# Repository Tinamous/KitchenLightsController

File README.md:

# KitchenLightsController
IoT Particle Photon powered kitchen lights controller. Switch and dim LED and halogen lights.

Assembly
--------

Mount SMD components.

Solder on JP1, 12V DC power in.
For 2 & 3 min molex headers use sponge to keep connectors in place. Solder single pin, and then reflow that pushing the connector square to the board.
Solder JP35, JP47, JP34, JP48, JP49 - 3 pin molex connectors. Farnell: 9731156
Solder JP201, 202, 203, 301, 302, 303, 401, 402, 403. Optionally solder JP501 or 502. (or both). Fit only as many as you need. Farnell: 9731148

Solder JP43 (terminal block).

Fit C1 (330nF. Farnell: 1902922
Solder headers for Photon. eBay.
F1 Fuse folder. Farnell: 1453528
IC1 7805 or eBay switching version
C4 1000uF 16v. Farnell: 9693610
Connect JP37 if using onboard 5V supply for NeoPixels.
Fit X2 if using USB 5V switch.
Fuse 5A quick blow: Farnell: 1354578

Before powering up:
Check 12V rails for short circuit.
Check 5V rails for short.
Check 3v3 rails for short.

Power up using low current limit on bench PSU (ca. 50m-100A)
Check 5v rail and adjust reg as needed. Expect 3 LEDs to light (12v, 5V and ext. 5V). 14-20mA consumption.

V2.03 Changed:
Moved via under Photon to not mess with silk screen.
Moved OSH logo to near USB A Socket to give it more room and allow the 5V LED to be reverse mounted.
TODO:
Move 5V LED to be reverse mounted
Change 5V usb switched connector to be 0.1" molex not screw terminal.
Correct Channel 4 & Ext. 5V supply screw terminals to be the correct way around (double line on outside of the board).

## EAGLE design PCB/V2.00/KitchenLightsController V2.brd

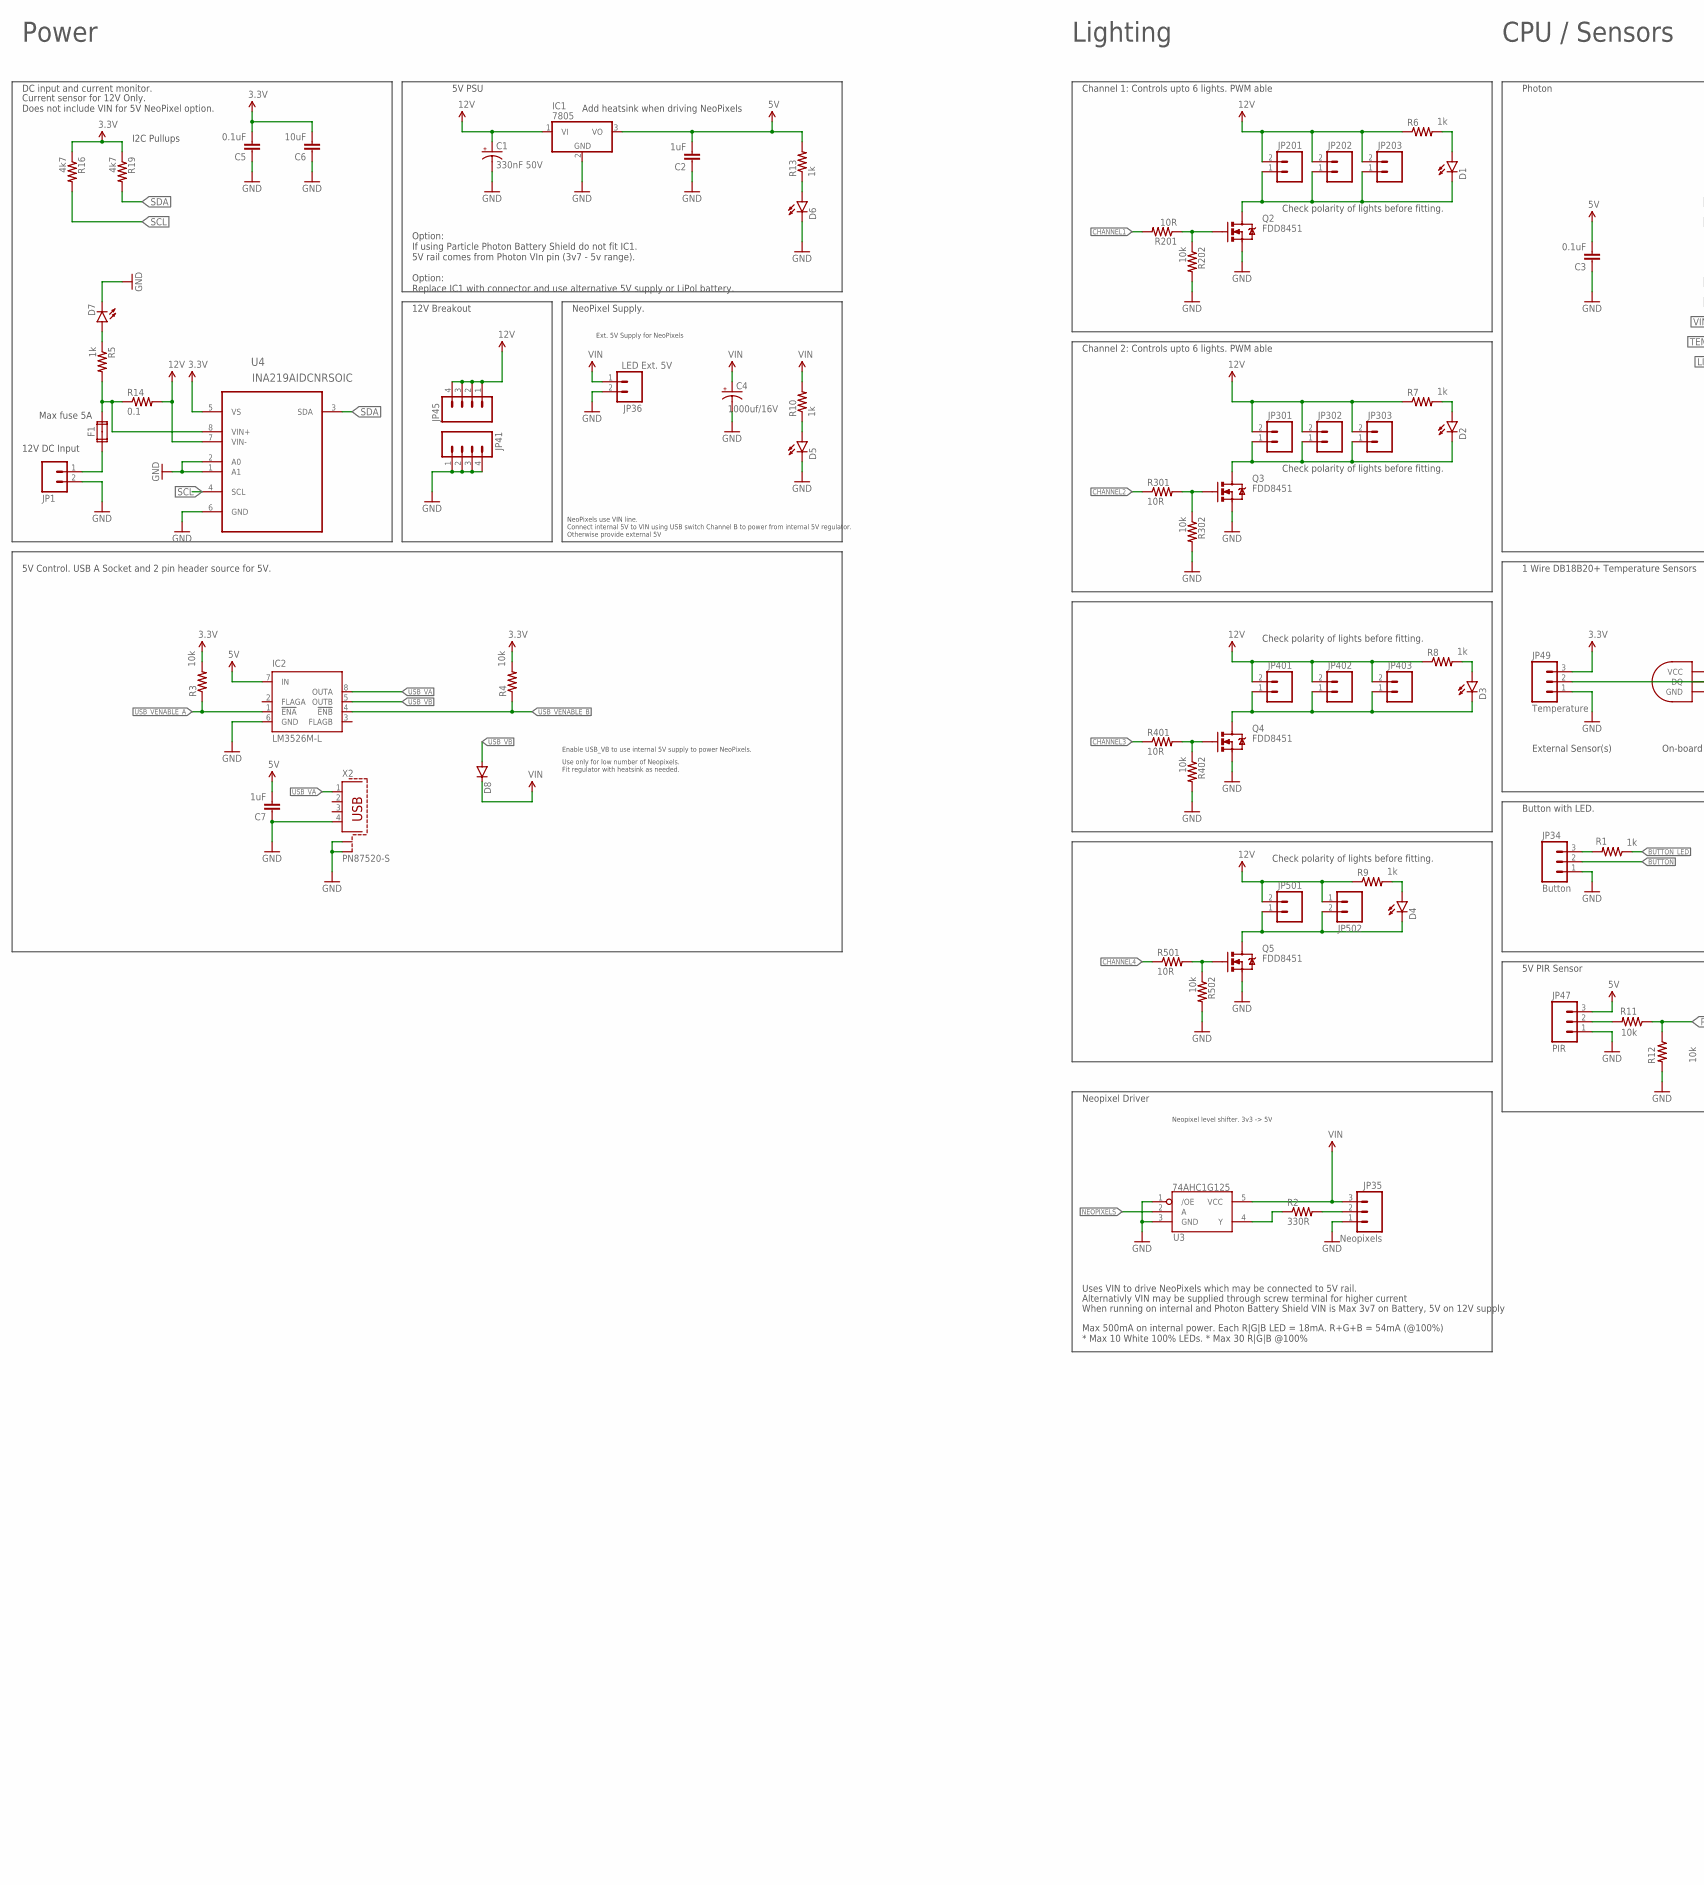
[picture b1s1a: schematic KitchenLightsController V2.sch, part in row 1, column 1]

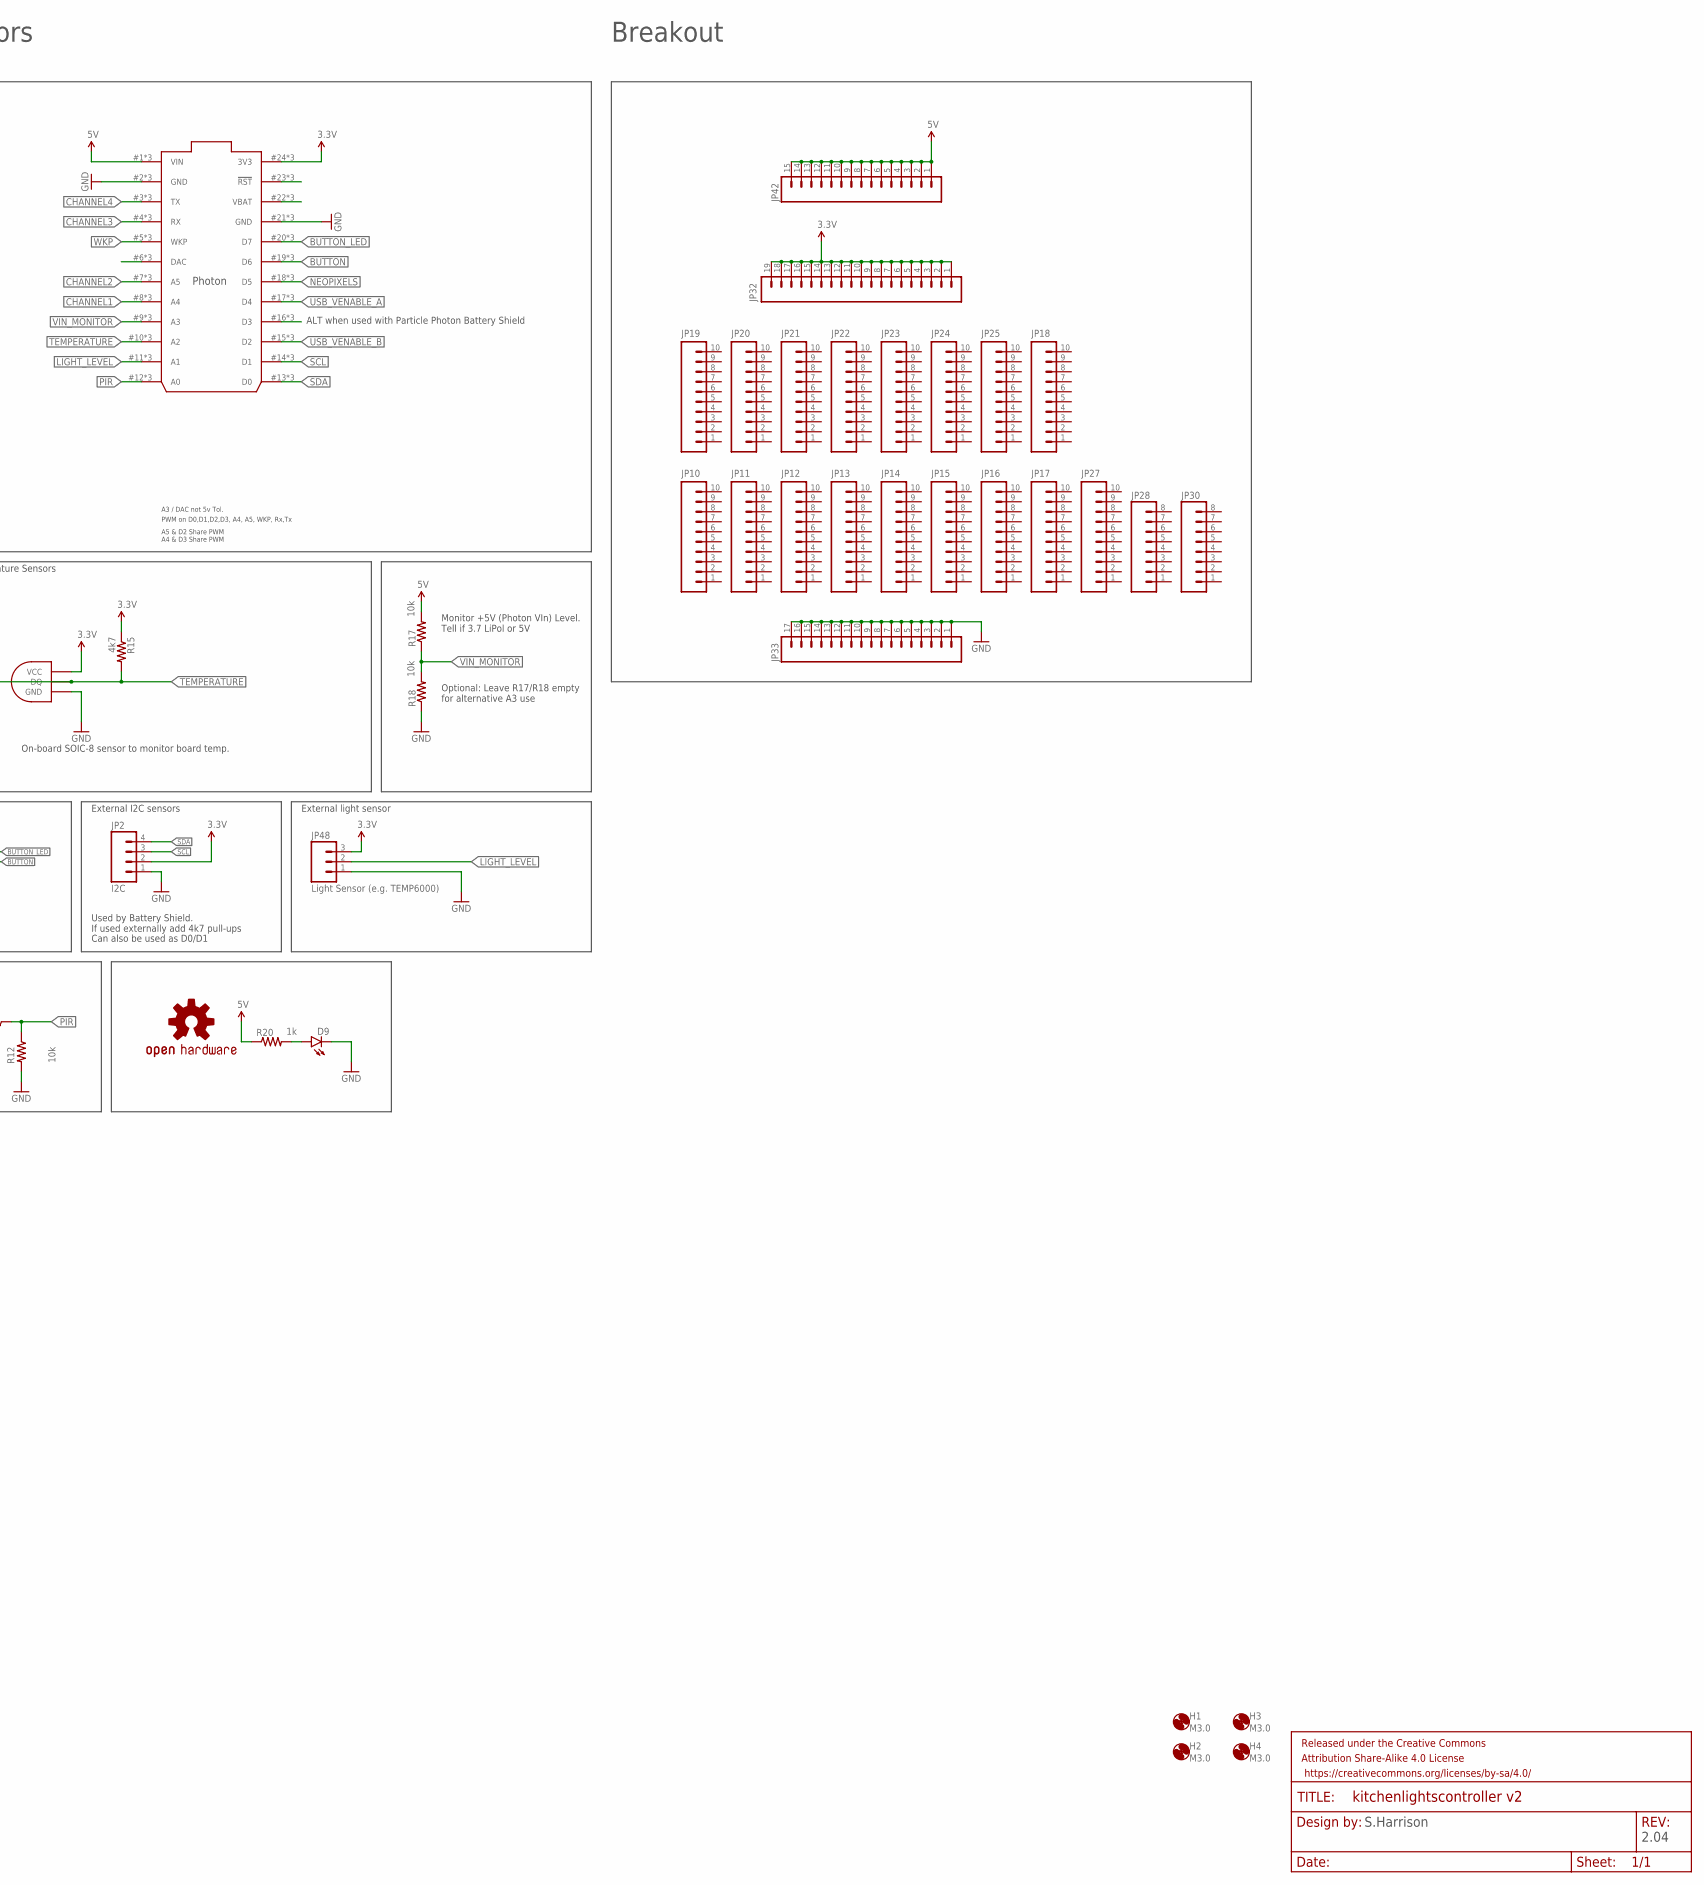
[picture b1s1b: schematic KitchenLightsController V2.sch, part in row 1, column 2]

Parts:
C1: 330nF 50V; CPOL-RADIAL-10UF-25V; FARNELL 1902922
C2, C7: 1uF; 0805-CAP
C3, C5: 0.1uF; 0805-CAP
C4: 1000uf/16V; CPOL-RADIAL-1000UF-25V-KIT; FARNELL 9693610
C6: 10uF; 0805-CAP
D1, D2, D3, D4, D5, D6, D7: GREEN; LED-1206
D8: DIODESMA-KIT; SMA-DIODE-KIT
D9: LED1206-BOTTOM; LED-1206-BOTTOM
F1: FUSE2P; FUSE1; FARNELL 1453528
FRAME1: FRAME-LETTER; CREATIVE_COMMONS
H1, H2, H3, H4: M3.0; 3,0
IC1: 7805; TO220V
IC2: LM3526M-L; SO08
JP1: M025MM; SCREWTERMINAL-5MM-2; FARNELL 2008197
JP2: I2C; 1X04
JP10, JP11, JP12, JP13, JP14, JP15, JP16, JP17, JP18, JP19, JP20, JP21, JP22, JP23, JP24, JP25, JP27: M10NO_SILK_PTH_FEMALE; 1X10_NO_SILK
JP28, JP30: M08NO_SILK_FEMALE_PTH; 1X08_NO_SILK
JP32: M191X19; 1X19
JP33: M17; 1X17
JP34: Button; MOLEX-1X3; FARNELL 9731156
JP35: Neopixels; MOLEX-1X3; FARNELL 9731156
JP36: LED Ext. 5V; SCREWTERMINAL-3.5MM-2
JP41, JP45: M04PTH; 1X04
JP42: M15; 1X15
JP47: PIR; MOLEX-1X3; FARNELL 9731156
JP48: Light Sensor (e.g. TEMP6000); MOLEX-1X3; FARNELL 9731156
JP49: Temperature; MOLEX-1X3; FARNELL 9731156
JP201, JP202, JP203, JP301, JP302, JP303, JP401, JP402, JP403, JP501: M02POLAR; MOLEX-1X2
JP502: M023.5MM; SCREWTERMINAL-3.5MM-2
LOGO1: OSHW-LOGOM; OSHW-LOGO-M
Q2, Q3, Q4, Q5: FDD8451; DPAK
R1, R5, R6, R7, R8, R9, R10, R13, R20: 1k; 0805
R2: 330R; 0805
R3, R4, R11, R12, R17, R18, R202, R302, R402, R502: 10k; 0805
R14: 0.1; 2512; FARNELL 1435947
R15, R16, R19: 4k7; 0805
R201, R301, R401, R501: 10R; 0805
U1: PHOTON_WITH_STACKABLE_HEADERS; PHOTON_STACKABLE
U2: DS1820SOIC; DS18B20_SOIC
U3: 74AHC1G125; SOT23-5
U4: INA219AIDCNRSOIC; SO08
X2: PN87520-S

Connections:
3.3V: C5.2, C6.2, JP2.2, JP32.1, JP32.2, JP32.3, JP32.4, JP32.5, JP32.6, JP32.7, JP32.8, JP32.9, JP32.10, JP32.11, JP32.12, JP32.13, JP32.14, JP32.15, JP32.16, JP32.17, JP32.18, JP32.19, JP48.3, JP49.3, R3.2, R4.2, R15.1, R16.1, R19.1, U1.24 (3V3), U1.#24 (3V3), U1.@24 (3V3), U2.VCC, U4.5 (VS)
5V: C2.2, C3.2, C7.2, IC1.3 (VO), IC2.7 (IN), JP42.1, JP42.2, JP42.3, JP42.4, JP42.5, JP42.6, JP42.7, JP42.8, JP42.9, JP42.10, JP42.11, JP42.12, JP42.13, JP42.14, JP42.15, JP47.3, R13.2, R17.2, R20.1, U1.1 (VIN), U1.#1 (VIN), U1.@1 (VIN)
12V: C1.1 (+), IC1.1 (VI), JP45.1, JP45.2, JP45.3, JP45.4, JP201.2, JP202.2, JP203.2, JP301.2, JP302.2, JP303.2, JP401.2, JP402.2, JP403.2, JP501.2, JP502.1, R6.1, R7.1, R8.1, R9.1, R14.2, U4.7 (VIN-)
BUTTON: JP34.2, U1.19 (D6), U1.#19 (D6), U1.@19 (D6)
BUTTON_LED: R1.1, U1.20 (D7), U1.#20 (D7), U1.@20 (D7)
CHANNEL1: R201.2, U1.8 (A4), U1.#8 (A4), U1.@8 (A4)
CHANNEL2: R301.1, U1.7 (A5), U1.#7 (A5), U1.@7 (A5)
CHANNEL3: R401.1, U1.4 (RX), U1.#4 (RX), U1.@4 (RX)
CHANNEL4: R501.1, U1.3 (TX), U1.#3 (TX), U1.@3 (TX)
CHANNEL_1_SWITCHED: D1.C, JP201.1, JP202.1, JP203.1, Q2.4 (D)
CHANNEL_2_SWITCHED: D2.C, JP301.1, JP302.1, JP303.1, Q3.4 (D)
CHANNEL_3_SWITCHED: D3.C, JP401.1, JP402.1, JP403.1, Q4.4 (D)
CHANNEL_4_SWITCHED: D4.C, JP501.1, JP502.2, Q5.4 (D)
D3: U1.16 (D3), U1.#16 (D3), U1.@16 (D3)
DAC: U1.6 (DAC), U1.#6 (DAC), U1.@6 (DAC)
GND: C1.2 (-), C2.1, C3.1, C4.-, C5.1, C6.1, C7.1, D5.C, D6.C, D7.C, D9.C, IC1.2 (GND), IC2.6 (GND), JP1.2, JP2.1, JP33.1, JP33.2, JP33.3, JP33.4, JP33.5, JP33.6, JP33.7, JP33.8, JP33.9, JP33.10, JP33.11, JP33.12, JP33.13, JP33.14, JP33.15, JP33.16, JP33.17, JP34.1, JP35.1, JP36.2, JP41.1, JP41.2, JP41.3, JP41.4, JP47.1, JP48.1, JP49.1, Q2.3 (S), Q3.3 (S), Q4.3 (S), Q5.3 (S), R12.2, R18.1, R202.2, R302.2, R402.2, R502.2, U1.2 (GND), U1.21 (GND), U1.#2 (GND), U1.#21 (GND), U1.@2 (GND), U1.@21 (GND), U2.GND, U3.1 (/OE), U3.3 (GND), U4.1 (A1), U4.2 (A0), U4.6 (GND), X2.4, X2.S1, X2.S2
LIGHT_LEVEL: JP48.2, U1.11 (A1), U1.#11 (A1), U1.@11 (A1)
unnamed: D7.A, R5.1
unnamed: Q2.1 (G), R201.1, R202.1
unnamed: Q3.1 (G), R301.2, R302.1
unnamed: Q4.1 (G), R401.2, R402.1
unnamed: F1.2A, R5.2, R14.1, U4.8 (VIN+)
unnamed: R2.1, U3.4 (Y)
unnamed: Q5.1 (G), R501.2, R502.1
unnamed: JP35.2, R2.2
unnamed: D9.A, R20.2
unnamed: F1.1A, JP1.1
unnamed: JP34.3, R1.2
unnamed: D6.A, R13.1
unnamed: D5.A, R10.1
unnamed: D4.A, R9.2
unnamed: D3.A, R8.2
unnamed: JP47.2, R11.2
unnamed: D2.A, R7.2
unnamed: D1.A, R6.2
NEOPIXELS: U1.18 (D5), U1.#18 (D5), U1.@18 (D5), U3.2 (A)
PIR: R11.1, R12.1, U1.12 (A0), U1.#12 (A0), U1.@12 (A0)
RST: U1.23 (!RST), U1.#23 (!RST), U1.@23 (!RST)
SCL: JP2.3, R16.2, U1.14 (D1), U1.#14 (D1), U1.@14 (D1), U4.4 (SCL)
SDA: JP2.4, R19.2, U1.13 (D0), U1.#13 (D0), U1.@13 (D0), U4.3 (SDA)
TEMPERATURE: JP49.2, R15.2, U1.10 (A2), U1.#10 (A2), U1.@10 (A2), U2.DQ
USB_VA: IC2.8 (OUTA), X2.1
USB_VB: D8.A, IC2.5 (OUTB)
USB_VENABLE_A: IC2.1 (!ENA), R3.1, U1.17 (D4), U1.#17 (D4), U1.@17 (D4)
USB_VENABLE_B: IC2.4 (!ENB), R4.1, U1.15 (D2), U1.#15 (D2), U1.@15 (D2)
VBAT: U1.22 (VBAT), U1.#22 (VBAT), U1.@22 (VBAT)
VIN: C4.+, D8.C, JP35.3, JP36.1, R10.2, U3.5 (VCC)
VIN_MONITOR: R17.1, R18.2, U1.9 (A3), U1.#9 (A3), U1.@9 (A3)
WKP: U1.5 (WKP), U1.#5 (WKP), U1.@5 (WKP)

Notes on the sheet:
Channel 1: Controls upto 6 lights. PWM able
Channel 2: Controls upto 6 lights. PWM able
Check polarity of lights before fitting.
S.Harrison
2.04
Enable USB_VB to use internal 5V supply to power NeoPixels.
Use only for low number of Neopixels. Fit regulator with heatsink as needed.
Neopixel level shifter. 3v3 -> 5V
A3 / DAC not 5v Tol.
PWM on D0,D1,D2,D3, A4, A5, WKP, Rx,Tx
A5 & D2 Share PWM A4 & D3 Share PWM
5V PIR Sensor
12V Breakout
Monitor +5V (Photon VIn) Level. Tell if 3.7 LiPol or 5V
Optional: Leave R17/R18 empty for alternative A3 use
ALT when used with Particle Photon Battery Shield
5V PSU
Option: If using Particle Photon Battery Shield do not fit IC1. 5V rail comes from Photon VIn pin (3v7 - 5v range). Option: Replace IC1 with connector and use alternative 5V supply or LiPol battery.
DC input and current monitor.
12V DC Input
Max fuse 5A
Power
Lighting
CPU / Sensors
Breakout
On-board SOIC-8 sensor to monitor board temp.
External Sensor(s)
1 Wire DB18B20+ Temperature Sensors
Button with LED.
External I2C sensors
Used by Battery Shield. If used externally add 4k7 pull-ups
Can also be used as D0/D1
External light sensor
Photon
Neopixel Driver
Uses VIN to drive NeoPixels which may be connected to 5V rail.
Alternativly VIN may be supplied through screw terminal for higher current
When running on internal and Photon Battery Shield VIN is Max 3v7 on Battery, 5V on 12V supply
Max 500mA on internal power. Each R|G|B LED = 18mA. R+G+B = 54mA (@100%) * Max 10 White 100% LEDs. * Max 30 R|G|B @100%
NeoPixel Supply.

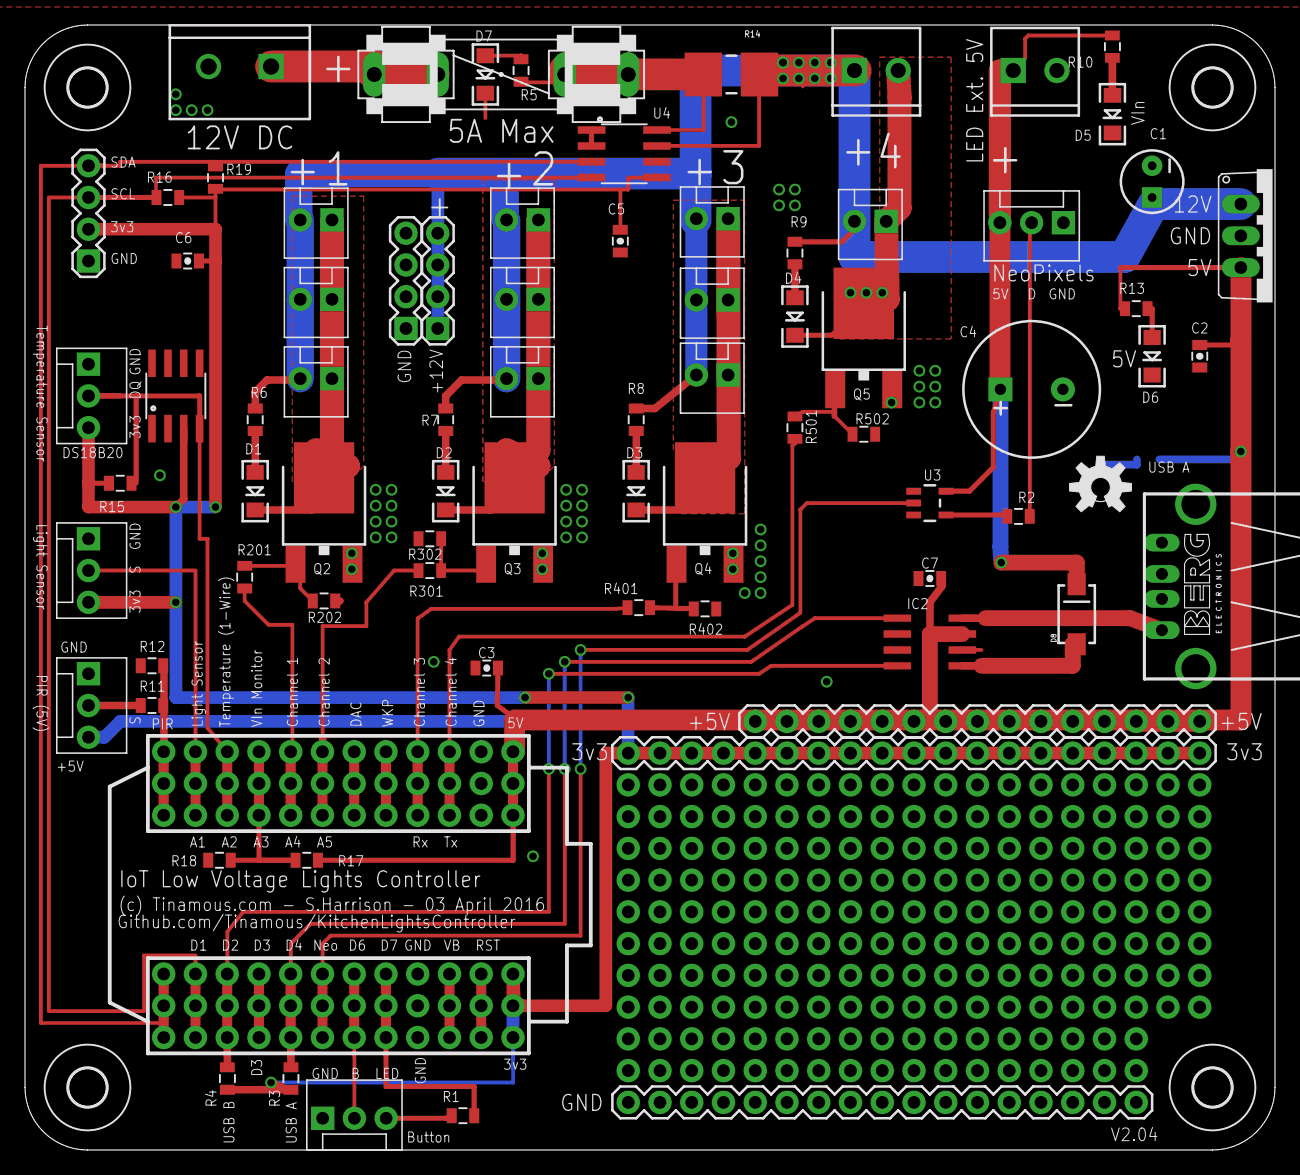
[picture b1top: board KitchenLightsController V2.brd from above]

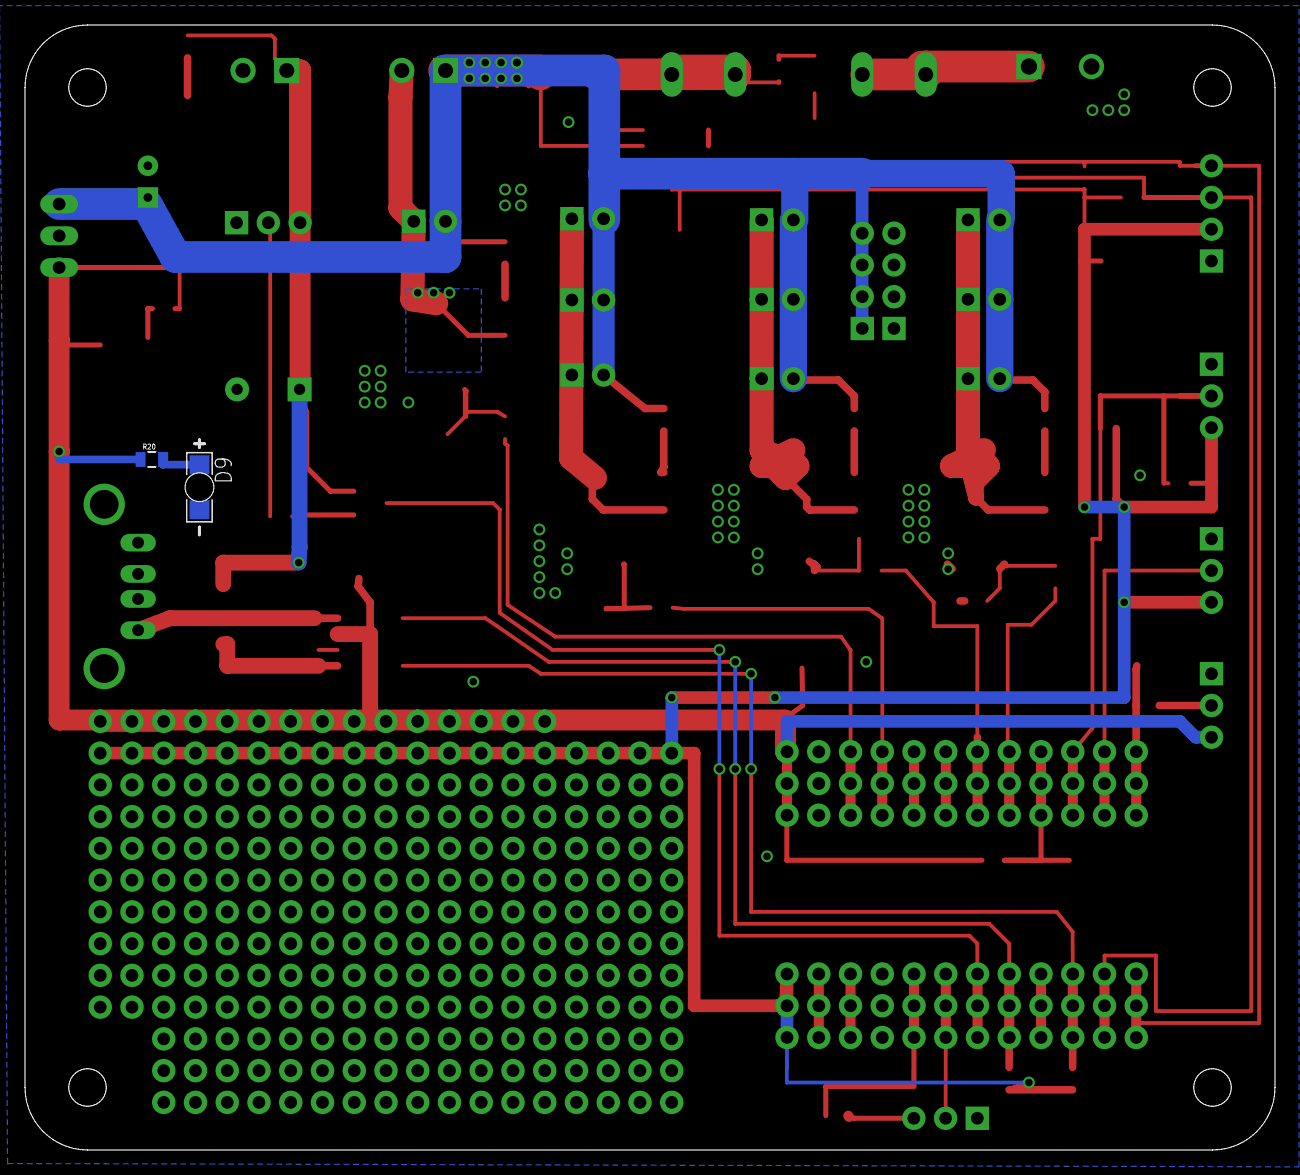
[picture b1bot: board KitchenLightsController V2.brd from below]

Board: 2 copper layers, 100.0 x 90.0 mm, 105 parts (2 on the bottom side), 49 nets.

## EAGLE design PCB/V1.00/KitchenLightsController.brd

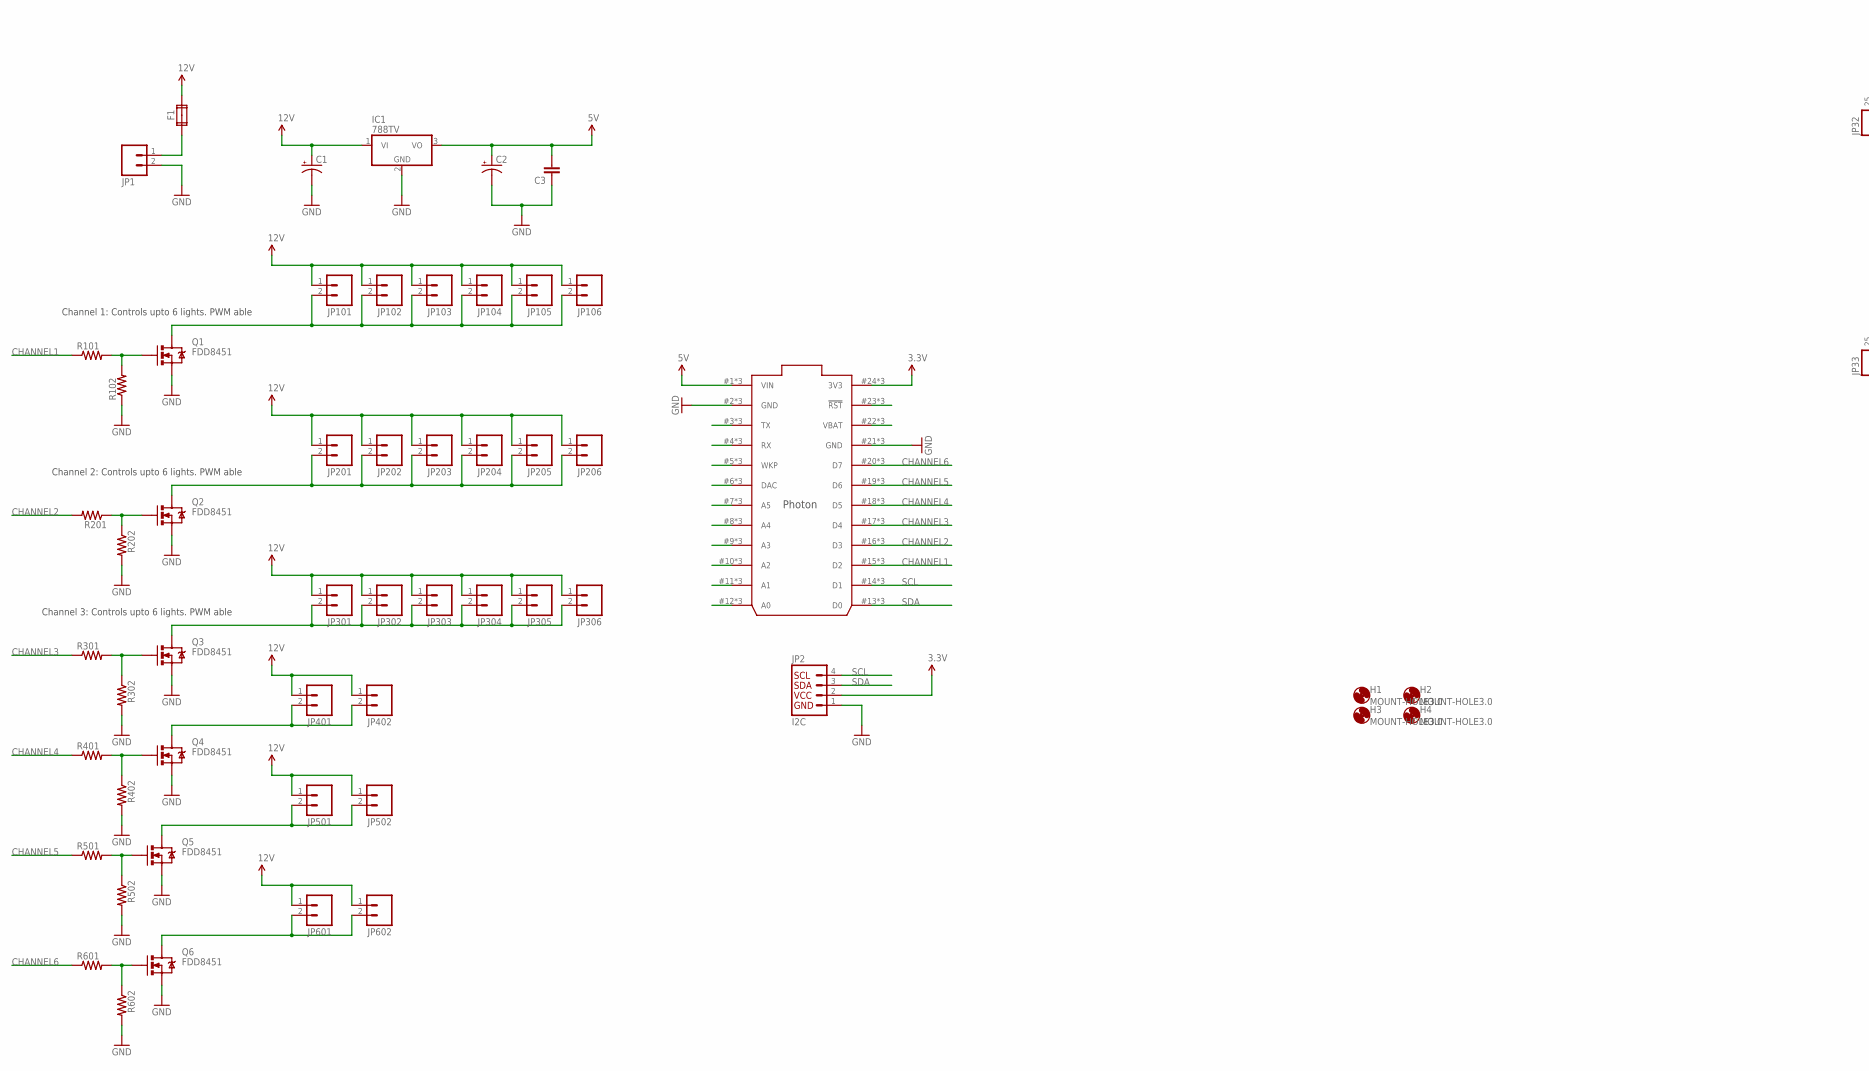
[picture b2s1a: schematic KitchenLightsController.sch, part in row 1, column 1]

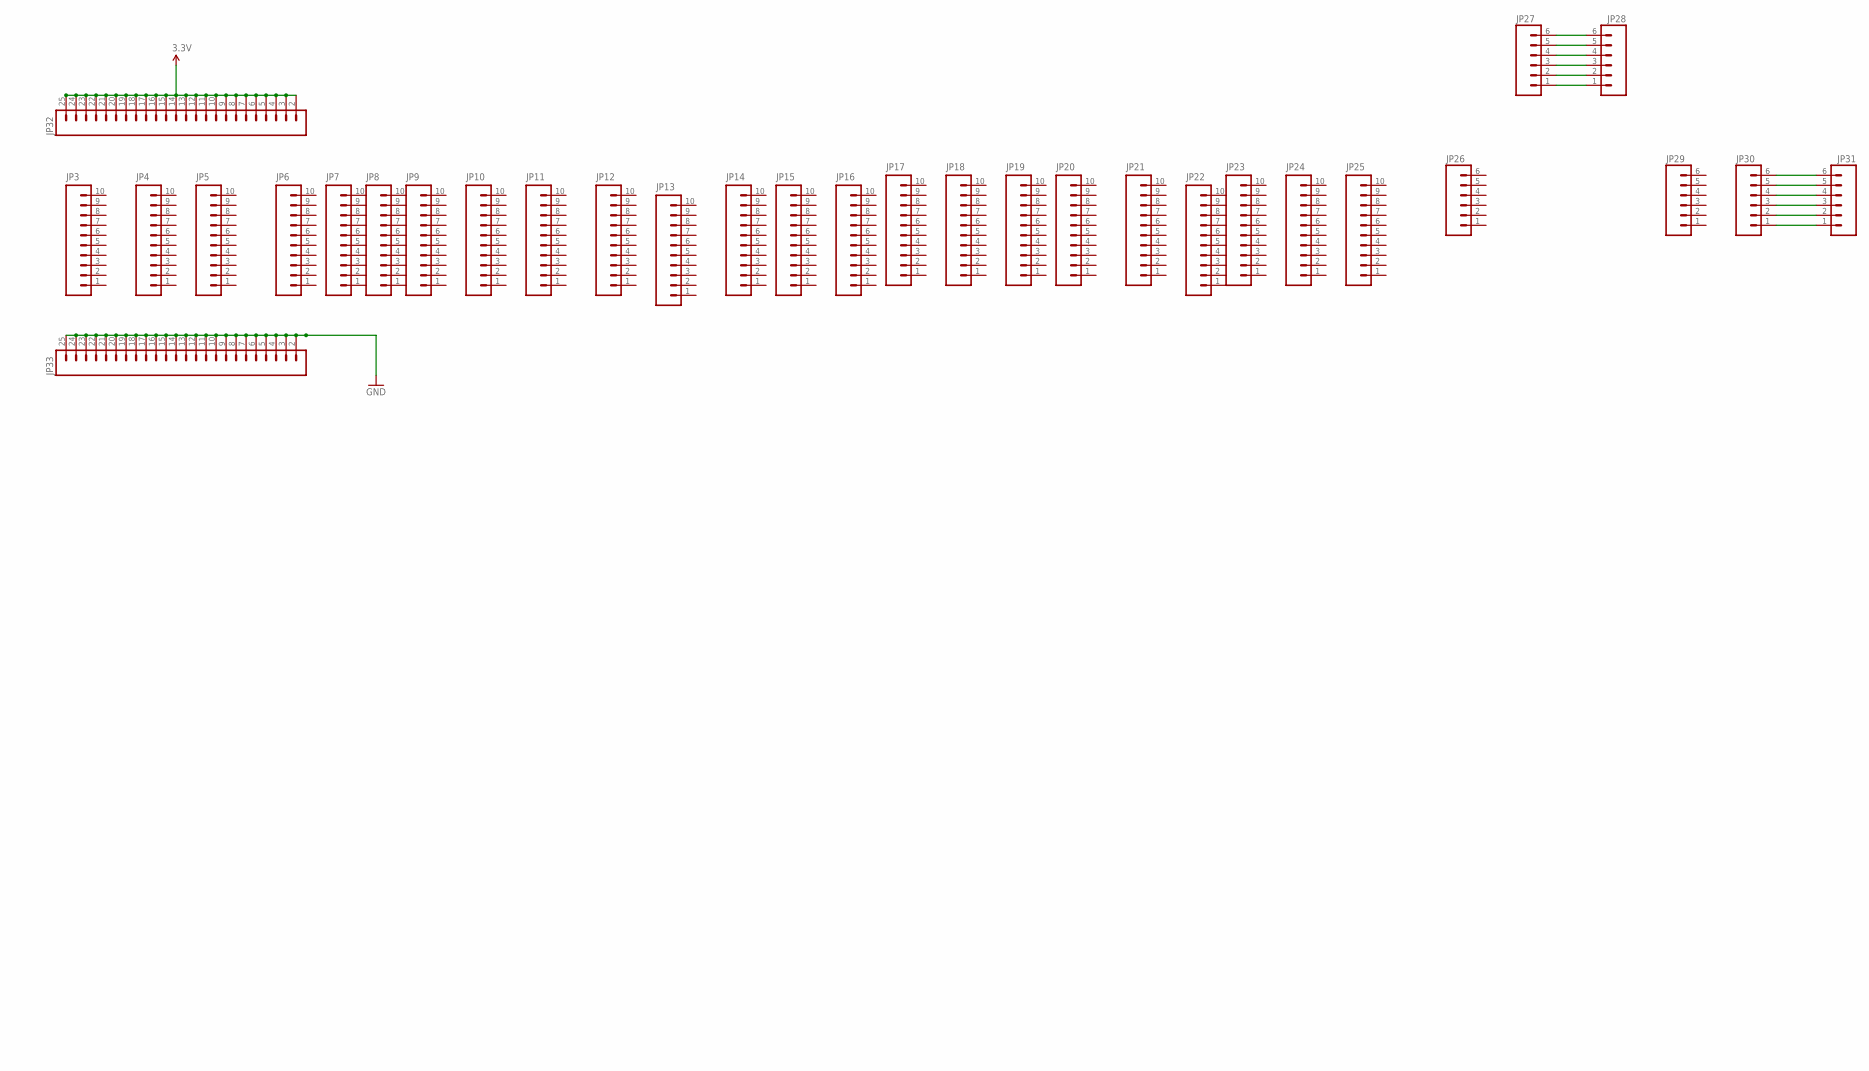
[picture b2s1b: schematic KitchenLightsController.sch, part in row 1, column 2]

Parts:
C1, C2: 10UF-25V-20%(PTH); CPOL-RADIAL-10UF-25V
C3: 1UF-25V-10%(0805)"; 0805-CAP
F1: FUSE2P; FUSE1
H1, H2, H3, H4: MOUNT-HOLE3.0; 3,0
IC1: 788TV; TO220V
JP1, JP402, JP502, JP602: M023.5MM; SCREWTERMINAL-3.5MM-2
JP2: I2C; 1X04
JP3, JP4, JP5, JP6, JP7, JP8, JP9, JP10, JP11, JP12, JP13, JP14, JP15, JP16, JP17, JP18, JP19, JP20, JP21, JP22, JP23, JP24, JP25: M10NO_SILK_PTH_FEMALE; 1X10_NO_SILK
JP26, JP27, JP28, JP29, JP30, JP31: M06NO_SILK_FEMALE_PTH; 1X06_NO_SILK
JP32, JP33: M24; 1X24
JP101, JP102, JP103, JP104, JP105, JP106, JP201, JP202, JP203, JP204, JP205, JP206, JP301, JP302, JP303, JP304, JP305, JP306, JP401, JP501, JP601: M02POLAR; MOLEX-1X2
Q1, Q2, Q3, Q4, Q5, Q6: FDD8451; DPAK
R101, R102, R201, R202, R301, R302, R401, R402, R501, R502, R601, R602: RESISTOR0805-RES; 0805
U$1: PHOTON_WITH_STACKABLE_HEADERS; PHOTON_STACKABLE

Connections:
3.3V: JP2.2, JP32.2, JP32.3, JP32.4, JP32.5, JP32.6, JP32.7, JP32.8, JP32.9, JP32.10, JP32.11, JP32.12, JP32.13, JP32.14, JP32.15, JP32.16, JP32.17, JP32.18, JP32.19, JP32.20, JP32.21, JP32.22, JP32.23, JP32.24, JP32.25, U$1.24 (3V3), U$1.#24 (3V3), U$1.@24 (3V3)
5V: C2.1 (+), C3.2, IC1.3 (VO), U$1.1 (VIN), U$1.#1 (VIN), U$1.@1 (VIN)
12V: C1.1 (+), F1.2A, IC1.1 (VI), JP101.1, JP102.1, JP103.1, JP104.1, JP105.1, JP106.1, JP201.1, JP202.1, JP203.1, JP204.1, JP205.1, JP206.1, JP301.1, JP302.1, JP303.1, JP304.1, JP305.1, JP306.1, JP401.1, JP402.1, JP501.1, JP502.1, JP601.1, JP602.1
CHANNEL1: R101.1, U$1.15 (D2), U$1.#15 (D2), U$1.@15 (D2)
CHANNEL2: R201.2, U$1.16 (D3), U$1.#16 (D3), U$1.@16 (D3)
CHANNEL3: R301.1, U$1.17 (D4), U$1.#17 (D4), U$1.@17 (D4)
CHANNEL4: R401.1, U$1.18 (D5), U$1.#18 (D5), U$1.@18 (D5)
CHANNEL5: R501.1, U$1.19 (D6), U$1.#19 (D6), U$1.@19 (D6)
CHANNEL6: R601.1, U$1.20 (D7), U$1.#20 (D7), U$1.@20 (D7)
GND: C1.2 (-), C2.2 (-), C3.1, IC1.2 (GND), JP1.2, JP2.1, JP33.2, JP33.3, JP33.4, JP33.5, JP33.6, JP33.7, JP33.8, JP33.9, JP33.10, JP33.11, JP33.12, JP33.13, JP33.14, JP33.15, JP33.16, JP33.17, JP33.18, JP33.19, JP33.20, JP33.21, JP33.22, JP33.23, JP33.24, JP33.25, Q1.3 (S), Q2.3 (S), Q3.3 (S), Q4.3 (S), Q5.3 (S), Q6.3 (S), R102.1, R202.2, R302.2, R402.2, R502.2, R602.2, U$1.2 (GND), U$1.21 (GND), U$1.#2 (GND), U$1.#21 (GND), U$1.@2 (GND), U$1.@21 (GND)
unnamed: Q1.1 (G), R101.2, R102.2
unnamed: Q2.1 (G), R201.1, R202.1
unnamed: Q3.1 (G), R301.2, R302.1
unnamed: Q4.1 (G), R401.2, R402.1
unnamed: U$1.23 (!RST), U$1.#23 (!RST), U$1.@23 (!RST)
unnamed: U$1.22 (VBAT), U$1.#22 (VBAT), U$1.@22 (VBAT)
unnamed: Q5.1 (G), R501.2, R502.1
unnamed: Q6.1 (G), R601.2, R602.1
unnamed: JP201.2, JP202.2, JP203.2, JP204.2, JP205.2, JP206.2, Q2.4 (D)
unnamed: JP101.2, JP102.2, JP103.2, JP104.2, JP105.2, JP106.2, Q1.4 (D)
unnamed: F1.1A, JP1.1
unnamed: JP27.1, JP28.1
unnamed: U$1.12 (A0), U$1.#12 (A0), U$1.@12 (A0)
unnamed: U$1.11 (A1), U$1.#11 (A1), U$1.@11 (A1)
unnamed: U$1.10 (A2), U$1.#10 (A2), U$1.@10 (A2)
unnamed: U$1.9 (A3), U$1.#9 (A3), U$1.@9 (A3)
unnamed: U$1.8 (A4), U$1.#8 (A4), U$1.@8 (A4)
unnamed: U$1.7 (A5), U$1.#7 (A5), U$1.@7 (A5)
unnamed: U$1.6 (DAC), U$1.#6 (DAC), U$1.@6 (DAC)
unnamed: U$1.5 (WKP), U$1.#5 (WKP), U$1.@5 (WKP)
unnamed: U$1.4 (RX), U$1.#4 (RX), U$1.@4 (RX)
unnamed: U$1.3 (TX), U$1.#3 (TX), U$1.@3 (TX)
unnamed: JP27.2, JP28.2
unnamed: JP27.3, JP28.3
unnamed: JP27.4, JP28.4
unnamed: JP301.2, JP302.2, JP303.2, JP304.2, JP305.2, JP306.2, Q3.4 (D)
unnamed: JP27.5, JP28.5
unnamed: JP401.2, JP402.2, Q4.4 (D)
unnamed: JP501.2, JP502.2, Q5.4 (D)
unnamed: JP601.2, JP602.2, Q6.4 (D)
unnamed: JP27.6, JP28.6
unnamed: JP30.1, JP31.1
unnamed: JP30.2, JP31.2
unnamed: JP30.3, JP31.3
unnamed: JP30.4, JP31.4
unnamed: JP30.5, JP31.5
unnamed: JP30.6, JP31.6
SCL: JP2.4, U$1.14 (D1), U$1.#14 (D1), U$1.@14 (D1)
SDA: JP2.3, U$1.13 (D0), U$1.#13 (D0), U$1.@13 (D0)

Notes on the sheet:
Channel 1: Controls upto 6 lights. PWM able
Channel 2: Controls upto 6 lights. PWM able
Channel 3: Controls upto 6 lights. PWM able

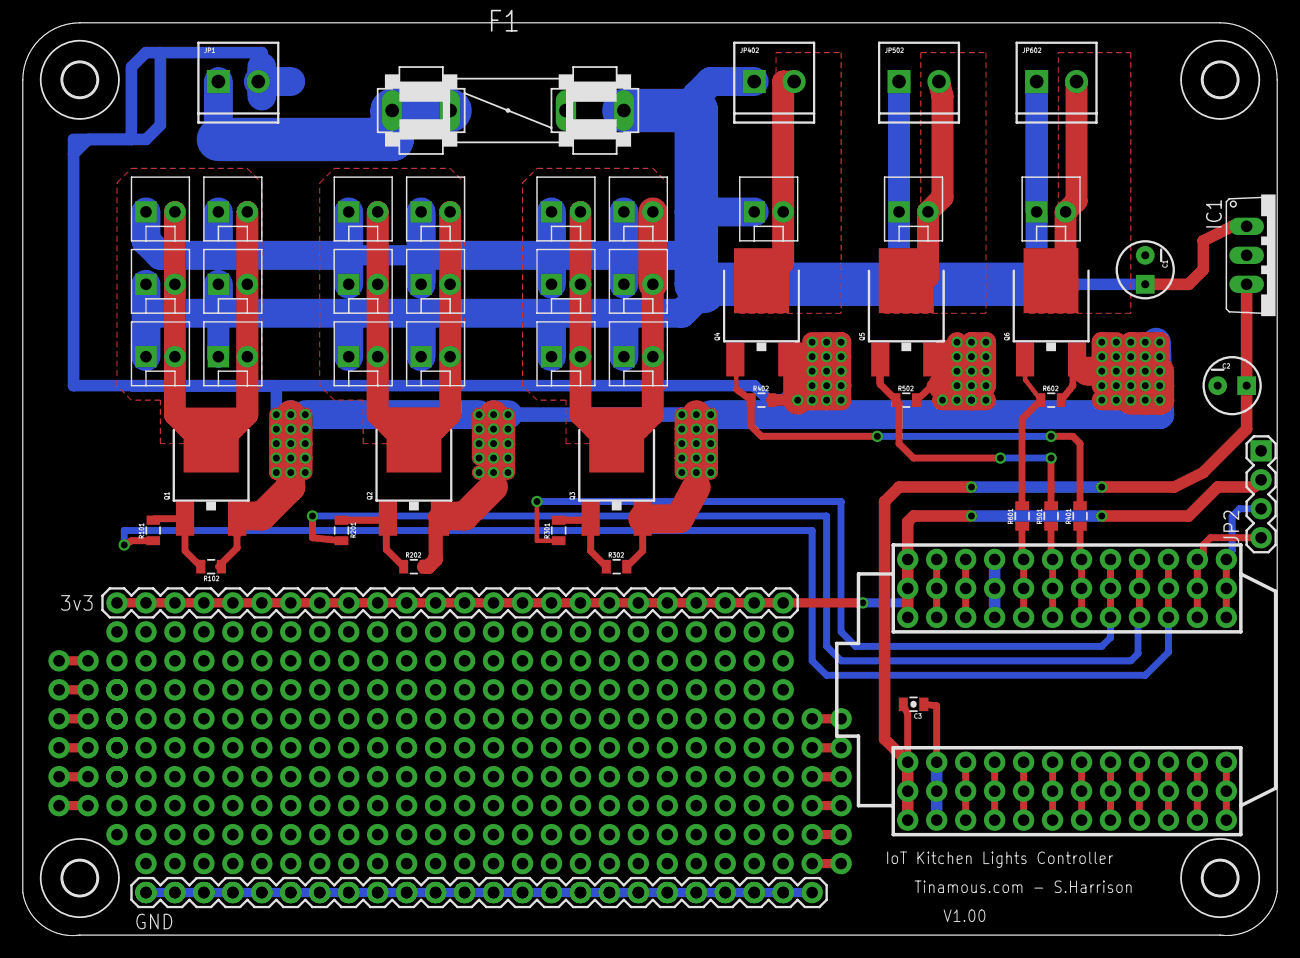
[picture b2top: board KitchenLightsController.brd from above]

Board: 2 copper layers, 110.0 x 80.0 mm, 85 parts (0 on the bottom side), 49 nets.

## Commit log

2015-12-08 Initial version - as sent to OSHPark.com
2016-01-19 Added V2 PCB. * Added PIR input * Added Light level input * Added Temperature sensor and 1 Wire temperature input * Added Switch + LED Input * Added VIn level sense * Removed Original channels 1 & 6 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
    Sent to DirtyPCB's for fab.
2016-02-05 Updated with minor tweaks and some additional component values specified from build of the v2.00 board.
2016-04-03 Corrected Gnd/+5V labels on NeoPixel connector which were the wrong way around.
    Moved Via from area under Photon as it messed with the text.
2016-04-03 Added assembly notes to readme file.
2016-04-03 Updated date on (c)
2016-04-03 Added 3D printable box.
2016-04-03 Moved + sign on NeoPixel input slightly to the left.
2016-04-03 Added reverse mount LED for OSH Logo.
    Modified USB channel B output to drive NeoPixels rather than using the jumper, as NeoPixels have a 1mA per pixel base current consumption this allows a string or NeoPixels to be switched off to save 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
2016-04-03 Made (hole for) switch optional.
    Improved lid.
    Reduced hole for power inlet
2016-04-05 Added gap between lid and base variable and reduced it to 0.3mm to provice a tighter fit.
2016-08-30 Adding initial version of the SmartThings device handler.
2016-08-30 Updated PCB pdfs
2016-08-30 Added firmware for the photon.

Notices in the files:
parts and their libraries:
SparkFun-Capacitors: Licensing: Creative Commons ShareAlike 4.0 International - https://creativecommons.org/licenses/by-sa/4.0
SparkFun-Aesthetics: Released under the Creative Commons Attribution Share-Alike 4.0 License
SparkFun-Aesthetics: https://creativecommons.org/licenses/by-sa/4.0
